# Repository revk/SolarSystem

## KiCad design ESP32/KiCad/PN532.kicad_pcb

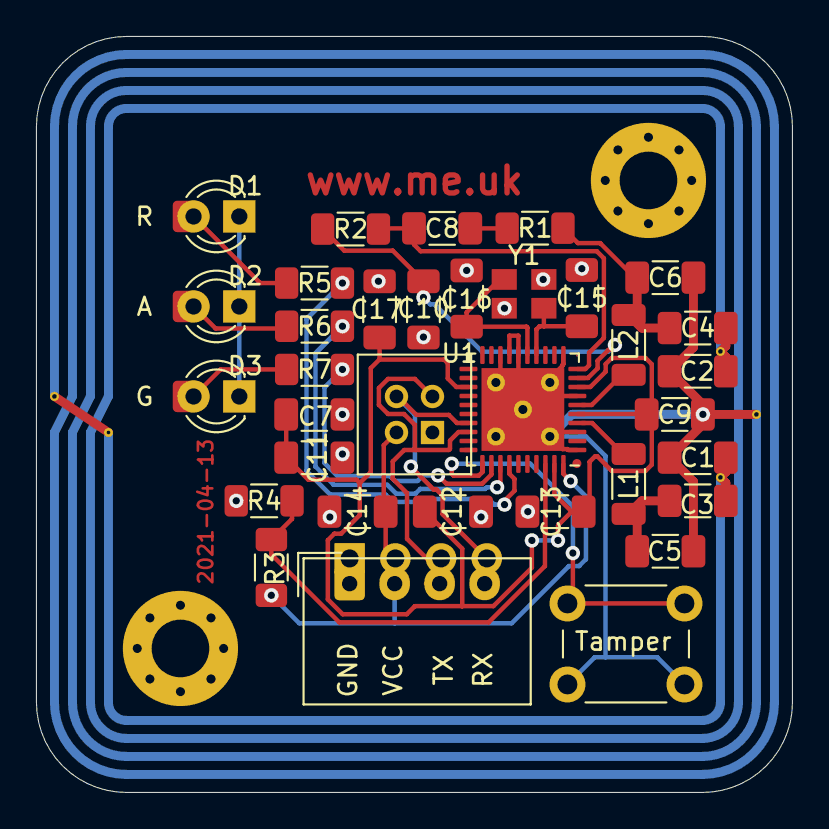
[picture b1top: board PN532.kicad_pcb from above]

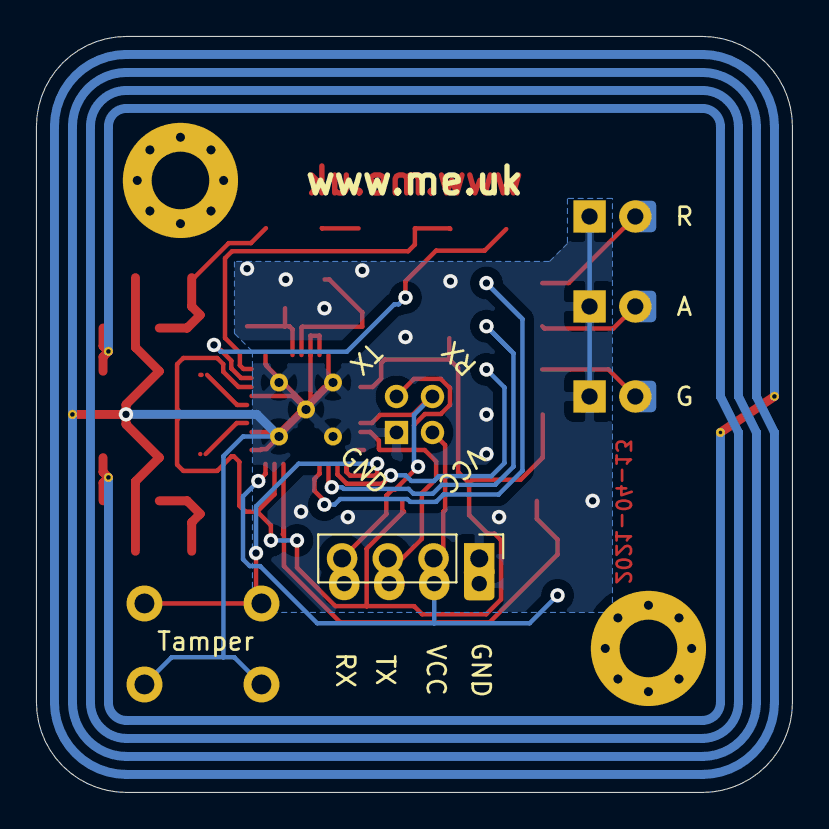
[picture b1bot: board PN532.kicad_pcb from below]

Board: 2 copper layers, 42.0 x 42.0 mm, 38 parts (2 on the bottom side), 24 nets.

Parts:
A1: PN532-Antenna
C1, C2: 200pF; C_1206_3216Metric_Pad1.33x1.80mm_HandSolder
C3, C4, C15, C16: 22pF; C_1206_3216Metric_Pad1.33x1.80mm_HandSolder
C5, C6: 220pF; C_1206_3216Metric_Pad1.33x1.80mm_HandSolder
C7, C10, C11, C12, C14, C17: 0.1uF; C_1206_3216Metric_Pad1.33x1.80mm_HandSolder
C8: 1nF; C_1206_3216Metric_Pad1.33x1.80mm_HandSolder
C9: 4.7uF; C_1206_3216Metric_Pad1.33x1.80mm_HandSolder
C13: 10uF; C_1206_3216Metric_Pad1.33x1.80mm_HandSolder
D1: RED; LED_D3.0mm_and_SMD
D2: AMBER; LED_D3.0mm_and_SMD
D3: GREEN; LED_D3.0mm_and_SMD
H1, H2: MountingHole; MountingHole_3.2mm_M3_Pad_Via
J1: Header; PinHeader_1x04_P2.54mm_Vertical
J2: SPOX; Molex_SPOX_5268-04A_1x04_P2.50mm_Horizontal
J3: MiniGrid; Connector-MilliGrid-2x2
L1, L2: 560nH; L_1206_3216Metric_Pad1.22x1.90mm_HandSolder
R1: 1K6; R_1206_3216Metric_Pad1.30x1.75mm_HandSolder
R2, R5, R6, R7: 1K; R_1206_3216Metric_Pad1.30x1.75mm_HandSolder
R3: 10K; R_1206_3216Metric_Pad1.30x1.75mm_HandSolder
R4: 20K; R_1206_3216Metric_Pad1.30x1.75mm_HandSolder
SW1: TAMPER; SW_PUSH_6mm
U1: PN532; QFN-40-(hand)-1EP_6x6mm_P0.5mm_EP4.6x4.6mm
Y1: 27.12MHz (Mouser 830053099); Crystal-3.4x2.7

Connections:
+3V3: C7.1, C9.1, C11.1, C12.1, C13.1, C17.1, U1.5, U1.8, U1.23, U1.39
+5V: C14.1, J1.2, J2.2, J3.2, R3.2, U1.40
GND: A1.2, C1.2, C2.1, C5.1, C6.1, C7.2, C9.2, C10.2, C11.2, C12.2, C13.2, C14.2, C15.2, C16.2, C17.2, D1.1, D2.1, D3.1, J1.1, J2.1, J3.1, R4.1, SW1.1, U1.1, U1.3, U1.7, U1.11, U1.16, U1.17, U1.18, U1.41, Y1.2, Y1.4
unnamed: A1.1, C1.1, C3.2
unnamed: A1.3, C2.2, C4.1
unnamed: C3.1, C5.2, L1.2
unnamed: C4.2, C6.2, L2.1, R1.2
unnamed: C8.1, R2.1, U1.10
unnamed: C8.2, R1.1
unnamed: C10.1, R2.2, U1.9
unnamed: C15.1, U1.14, Y1.1
unnamed: C16.1, U1.15, Y1.3
unnamed: D1.2, R5.2
unnamed: D2.2, R6.2
unnamed: D3.2, R7.2
unnamed: J1.3, J2.3, J3.3, U1.28
unnamed: J1.4, J2.4, J3.4, U1.27
unnamed: L1.1, U1.4
unnamed: L2.2, U1.6
unnamed: R3.1, R4.2, U1.38
unnamed: R5.1, U1.34
unnamed: R6.1, U1.33
unnamed: R7.1, U1.32
unnamed: SW1.2, U1.31

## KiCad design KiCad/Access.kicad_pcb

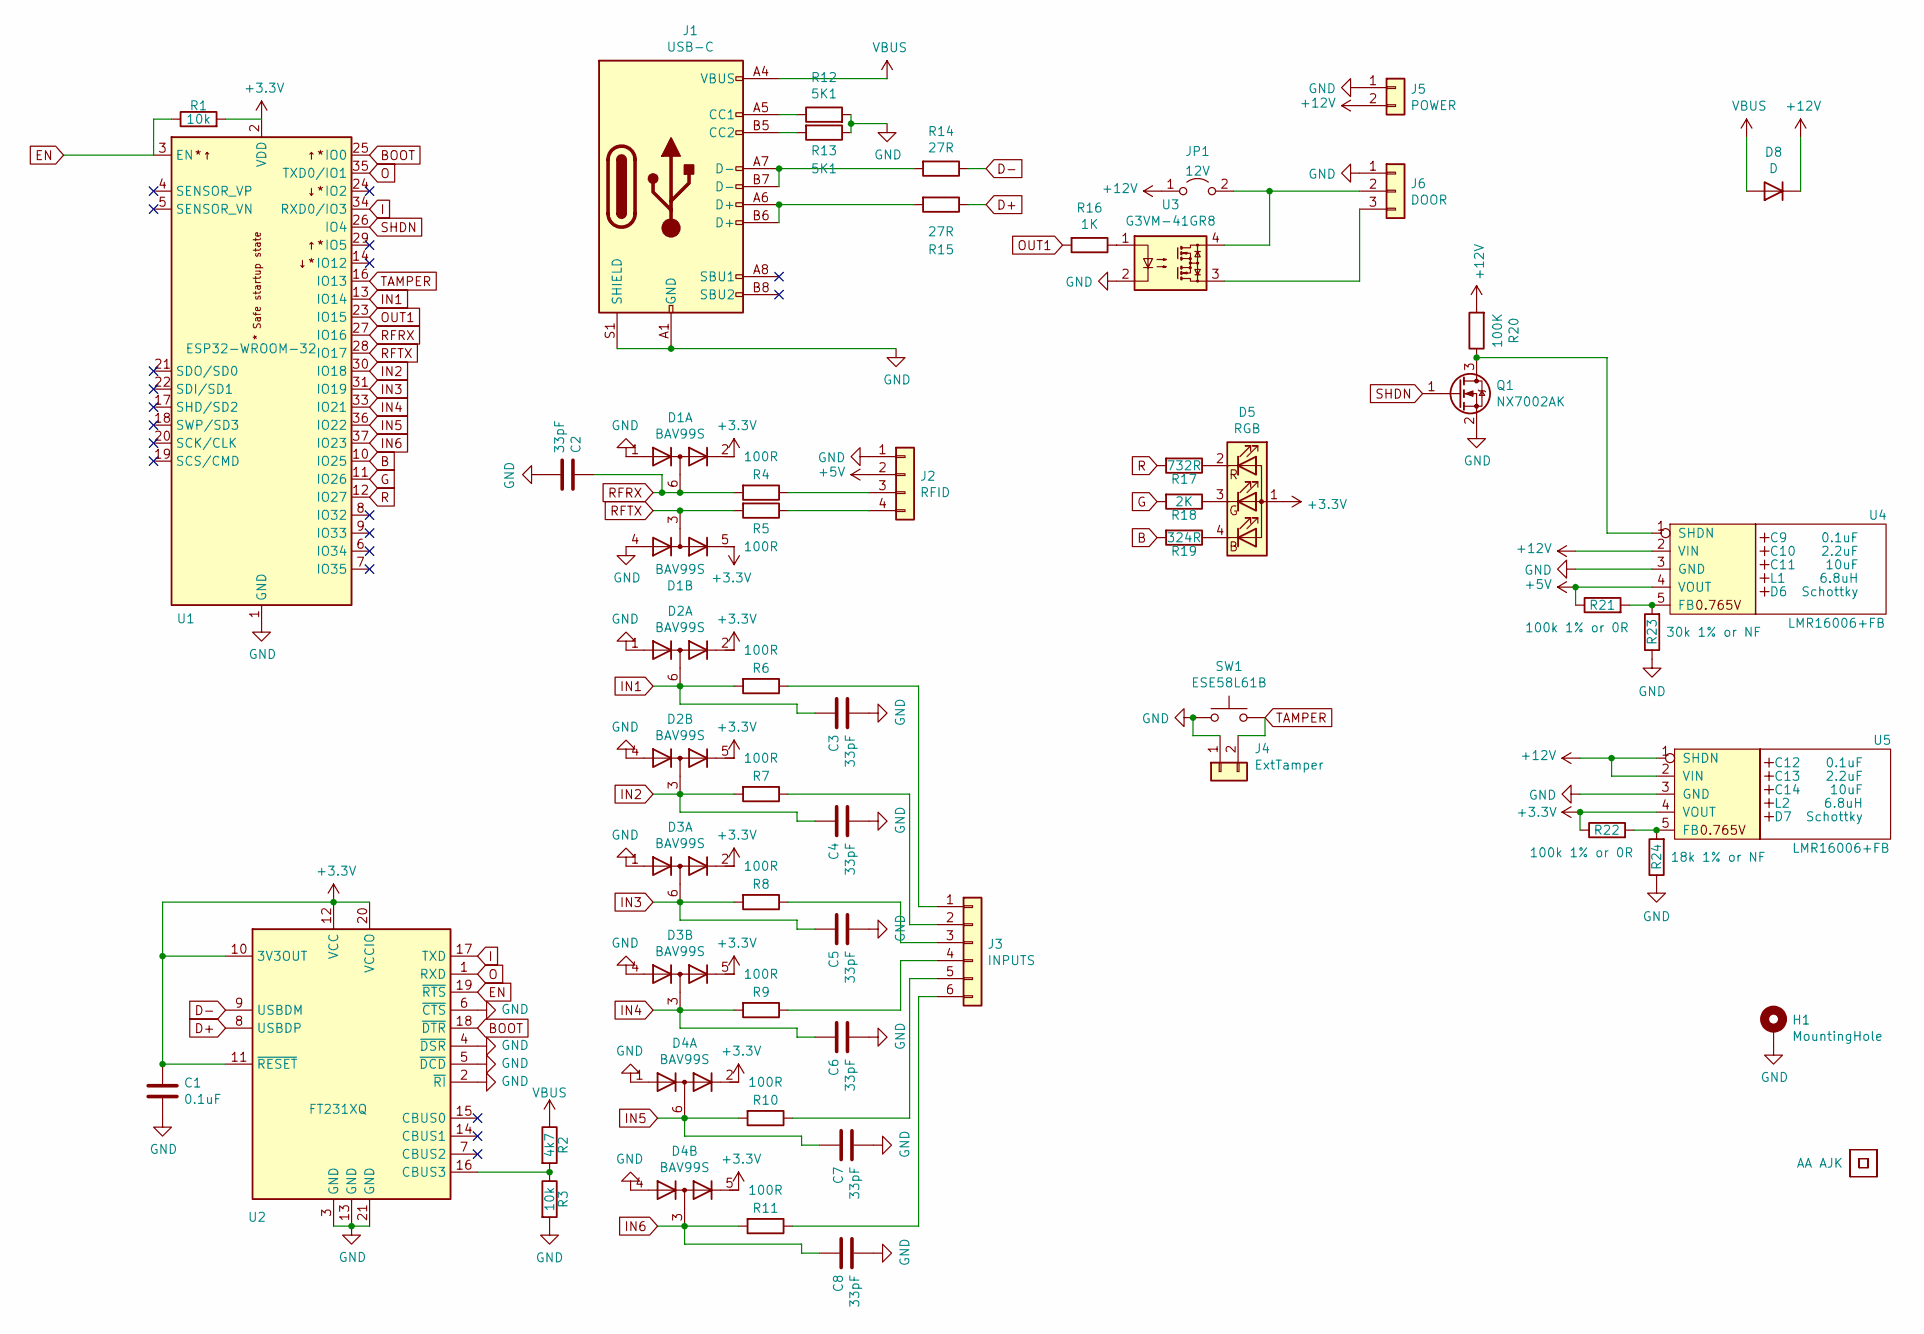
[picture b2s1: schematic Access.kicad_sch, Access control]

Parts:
AJK1: AJK
C1: 0.1uF; C_0603
C2, C3, C4, C5, C6, C7, C8: 33pF; C_0603
C9, C12: 0.1uF; Hidden
C10, C13: 2.2uF; Hidden
C11, C14: 10uF; Hidden
D1, D2, D3, D4: BAV99S; SOT-363_SC-70-6
D5: RGB; LED-RGB-1.6x1.6; Part No APTF1616LSEEZGKQBKC
D6, D7: Schottky; Hidden; Part No CD1206-B2100
D8: D; D_1206_3216Metric_Pad1.42x1.75mm_HandSolder
H1: MountingHole; ISO7380-M3-Pad
J1: USB-C; USC16-TR-Round
J2: RFID; Molex_MiniSPOX_H4RA
J3: INPUTS; Molex_MiniSPOX_H6RA
J4: ExtTamper; PinHeader_1x02_P2.54mm_Vertical
J5: POWER; Molex_MiniSPOX_H2RA
J6: DOOR; Molex_MiniSPOX_H3RA
JP1: 12V; PinHeader_1x02_P1.27mm_Vertical
L1, L2: 6.8uH; Hidden; Part No TYA4020
Q1: NX7002AK; SOT-23; Part No NX7002AK
R1, R3: 10k; R_0603
R2: 4k7; R_0603
R4, R5, R6, R7, R8, R9, R10, R11: 100R; R_0603
R12, R13: 5K1; R_0603
R14, R15: 27R; R_0603
R16: 1K; R_0603_1608Metric_Pad0.98x0.95mm_HandSolder
R17: 732R; R_0603
R18: 2K; R_0603
R19: 324R; R_0603
R20: 100K; R_0603
R21, R22: 100k 1% or 0R; R_0603
R23: 30k 1% or NF; R_0603
R24: 18k 1% or NF; R_0603
SW1: ESE58L61B; ESE58
U1: ESP32-WROOM-32
U2: FT231XQ; QFN-20-1EP_4x4mm_P0.5mm_EP2.5x2.5mm
U3: G3VM-41GR8; Special-SOP-4-3.7x4.55
U4, U5: LMR16006+FB; RegulatorBlockFB; Part No LMR16006YQ3
U6: AA
U7: QR; QR-SS

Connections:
+3V3: C1.1, D1.2 (K2), D1.5 (K4), D2.2 (K2), D2.5 (K4), D3.2 (K2), D3.5 (K4), D4.2 (K2), D4.5 (K4), D5.1 (A), R1.2, R22.1, U1.2 (VDD), U2.10 (3V3OUT), U2.11 (~RESET), U2.12 (VCC), U2.20 (VCCIO), U5.4 (VOUT)
+5V: J2.2, R21.1, U4.4 (VOUT)
+12V: D8.1 (K), J5.2, JP1.1 (A), R20.2, U4.2 (VIN), U5.1 (SHDN), U5.2 (VIN)
B: R19.2, U1.10 (IO25)
BOOT: U1.25 (IO0), U2.18 (~DTR)
D+: R15.1, U2.8 (USBDP)
D-: R14.1, U2.9 (USBDM)
EN: R1.1, U1.3 (EN), U2.19 (~RTS)
G: R18.2, U1.11 (IO26)
GND: C1.2, C2.2, C3.2, C4.2, C5.2, C6.2, C7.2, C8.2, D1.1 (A1), D1.4 (A3), D2.1 (A1), D2.4 (A3), D3.1 (A1), D3.4 (A3), D4.1 (A1), D4.4 (A3), H1.1, J1.A1 (GND), J1.A12 (GND), J1.B1 (GND), J1.B12 (GND), J1.S1 (SHIELD), J2.1, J4.1, J5.1, J6.1, Q1.2 (S), R3.2, R12.2, R13.1, R23.1, R24.1, SW1.1, U1.1 (GND), U1.15 (GND), U1.38 (GND), U1.39 (GND), U2.2 (~RI), U2.3 (GND), U2.4 (~DSR), U2.5 (~DCD), U2.6 (~CTS), U2.13 (GND), U2.21 (GND), U3.2, U4.3 (GND), U5.3 (GND)
I: U1.34 (RXD0/IO3), U2.17 (TXD)
IN1: C3.1, D2.6 (K3A4), R6.2, U1.13 (IO14)
IN2: C4.1, D2.3 (K1A2), R7.2, U1.30 (IO18)
IN3: C5.1, D3.6 (K3A4), R8.2, U1.31 (IO19)
IN4: C6.1, D3.3 (K1A2), R9.2, U1.33 (IO21)
IN5: C7.1, D4.6 (K3A4), R10.2, U1.36 (IO22)
IN6: C8.1, D4.3 (K1A2), R11.2, U1.37 (IO23)
unnamed: D5.2 (RK), R17.1
unnamed: D5.3 (GK), R18.1
unnamed: D5.4 (BK), R19.1
unnamed: J1.A5 (CC1), R12.1
unnamed: J1.A6 (D+), J1.B6 (D+), R15.2
unnamed: J1.A7 (D-), J1.B7 (D-), R14.2
unnamed: J1.B5 (CC2), R13.2
unnamed: J2.3, R4.1
unnamed: J2.4, R5.1
unnamed: J3.1, R6.1
unnamed: J3.2, R7.1
unnamed: J3.3, R8.1
unnamed: J3.4, R9.1
unnamed: J3.5, R10.1
unnamed: J3.6, R11.1
unnamed: J6.2, JP1.2 (B), U3.4
unnamed: J6.3, U3.3
unnamed: Q1.3 (D), R20.1, U4.1 (SHDN)
unnamed: R2.2, R3.1, U2.16 (CBUS3)
unnamed: R16.1, U3.1
unnamed: R21.2, R23.2, U4.5 (FB)
unnamed: R22.2, R24.2, U5.5 (FB)
O: U1.35 (TXD0/IO1), U2.1 (RXD)
OUT1: R16.2, U1.23 (IO15)
R: R17.2, U1.12 (IO27)
RFRX: C2.1, D1.6 (K3A4), R4.2, U1.27 (IO16)
RFTX: D1.3 (K1A2), R5.2, U1.28 (IO17)
SHDN: Q1.1 (G), U1.26 (IO4)
TAMPER: J4.2, SW1.2, U1.16 (IO13)
VBUS: D8.2 (A), J1.A4 (VBUS), J1.A9 (VBUS), J1.B4 (VBUS), J1.B9 (VBUS), R2.1

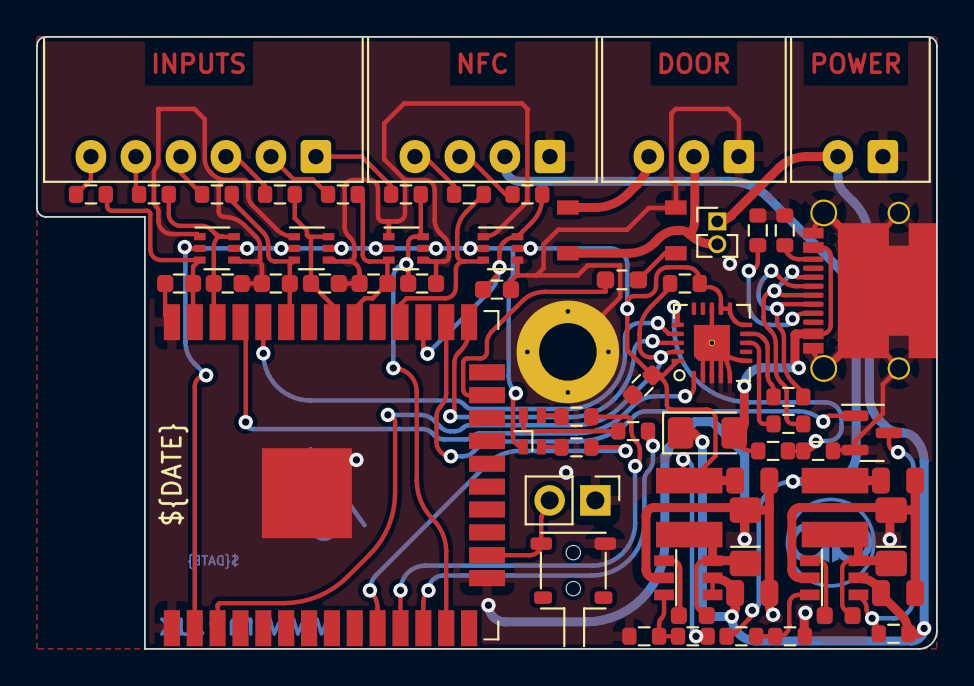
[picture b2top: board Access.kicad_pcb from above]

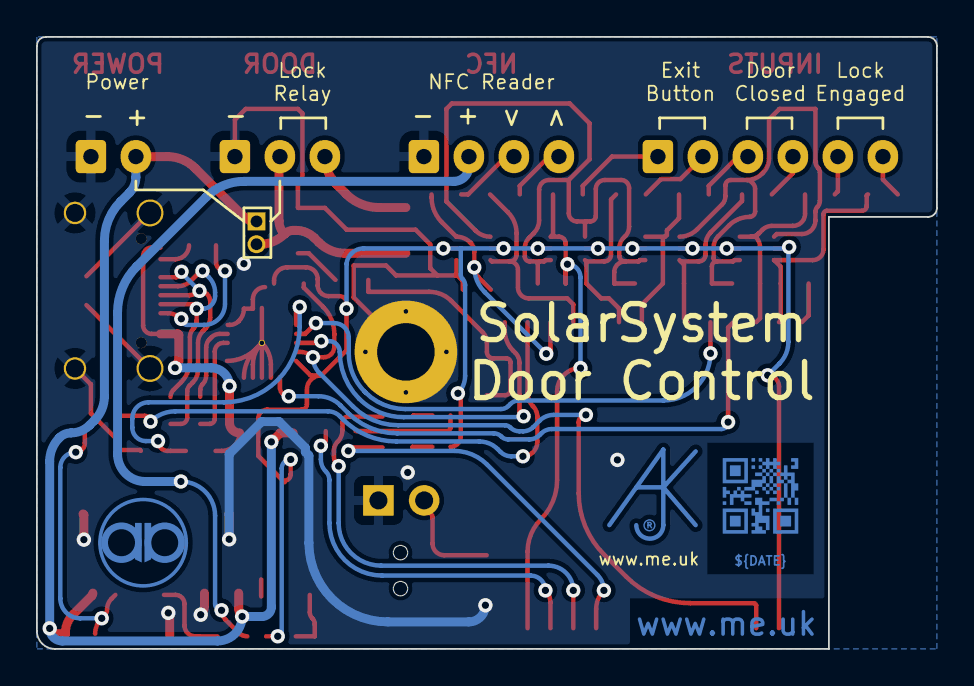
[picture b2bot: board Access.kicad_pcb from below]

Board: 2 copper layers, 50.0 x 34.0 mm, 66 parts (3 on the bottom side), 47 nets.

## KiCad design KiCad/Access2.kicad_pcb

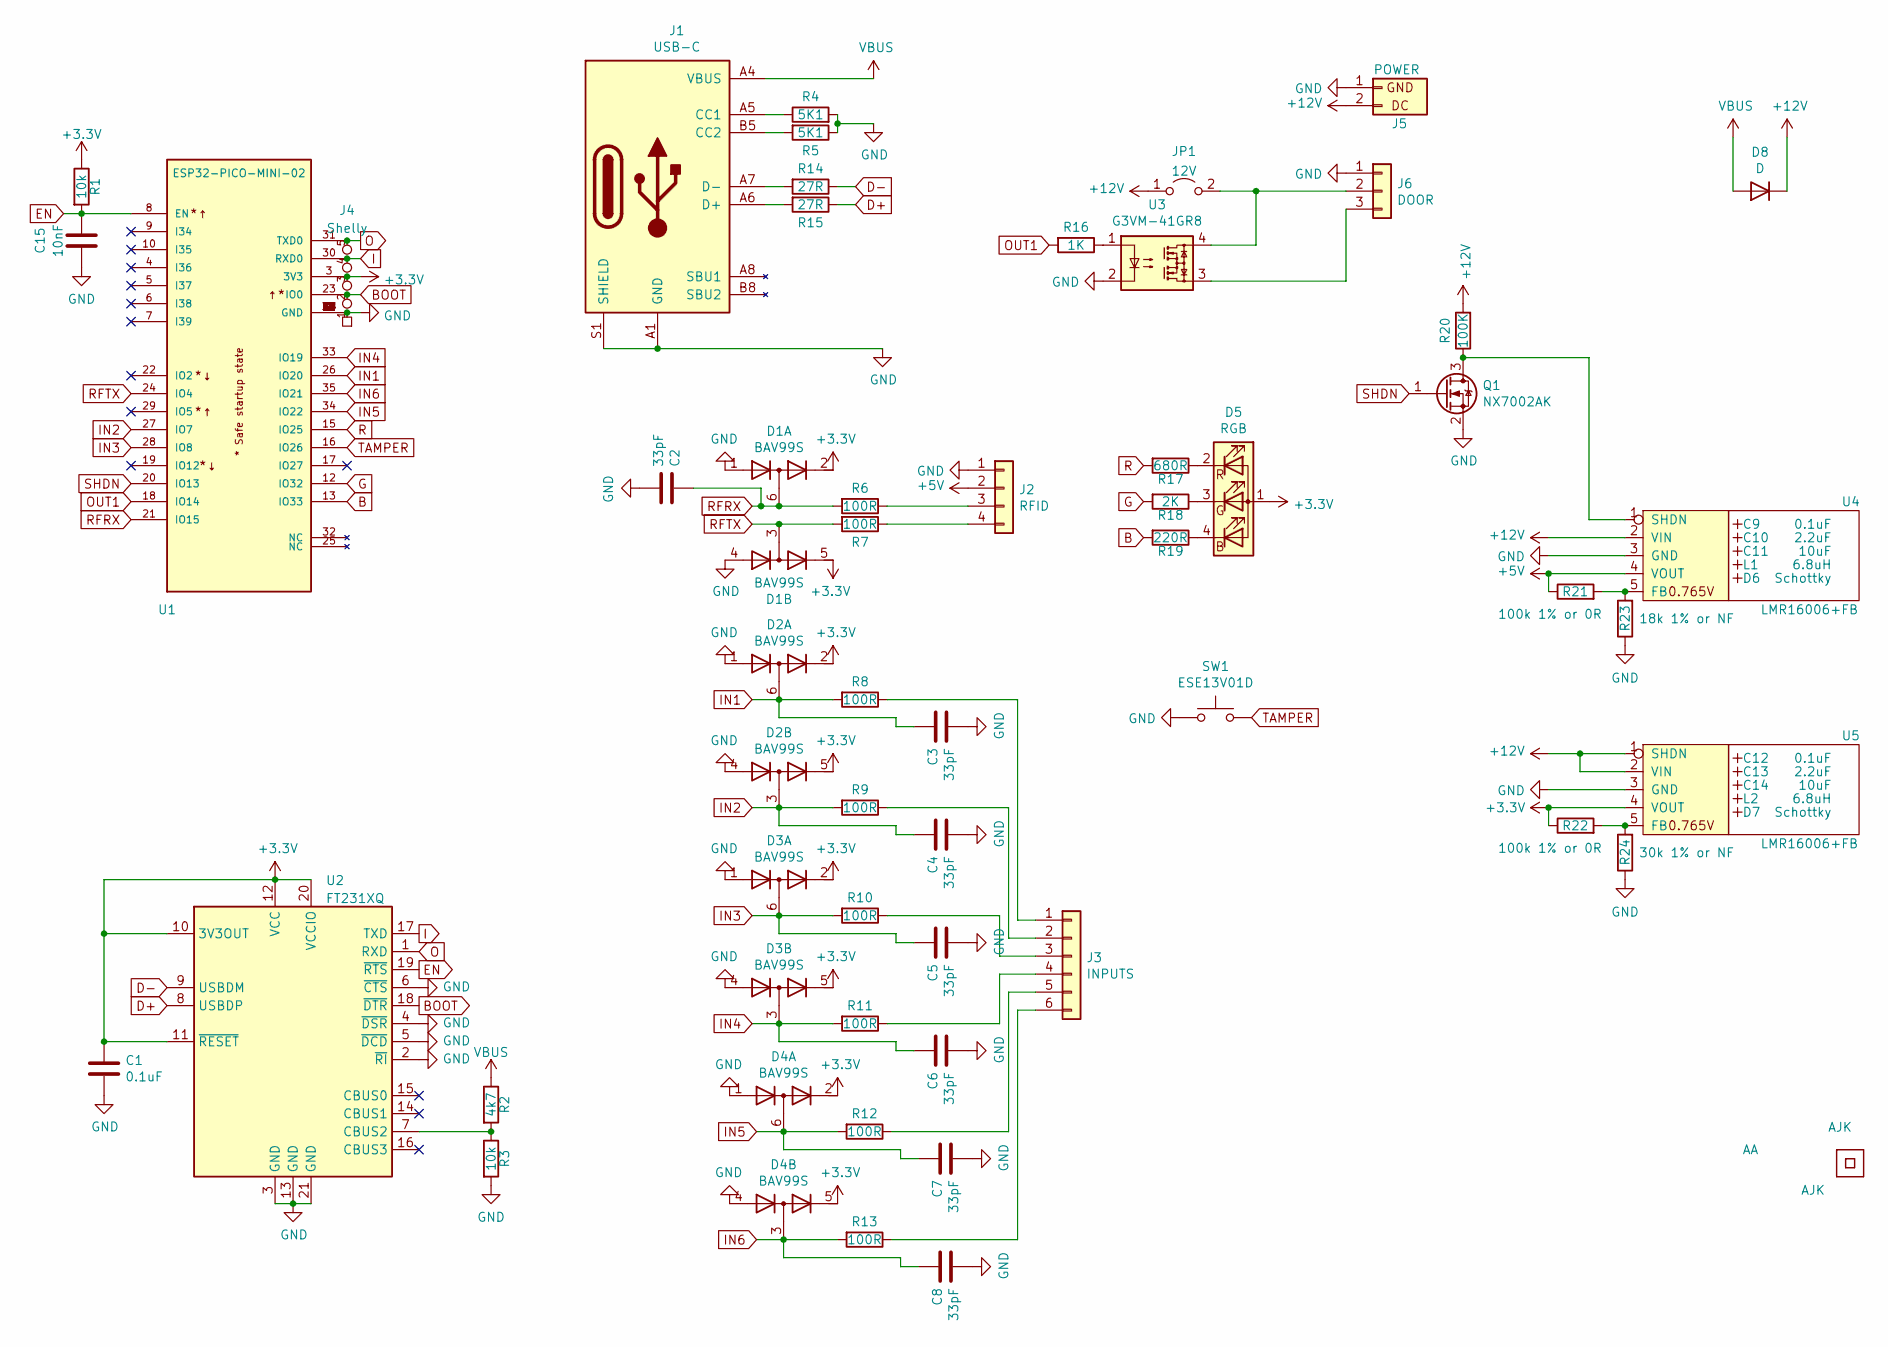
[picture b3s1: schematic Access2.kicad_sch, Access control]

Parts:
AJK1: AJK
C1: 0.1uF; C_0603
C2, C3, C4, C5, C6, C7, C8: 33pF; C_0603
C9, C12: 0.1uF; C_0603_
C10, C13: 2.2uF; C_0805_
C11, C14: 10uF; C_0805_
C15: 10nF; C_0603
D1, D2, D3, D4: BAV99S; SOT-363_SC-70-6
D5: RGB; LED-RGB-1.6x1.6; Part No APTF1616LSEEZGKQBKC
D6, D7: Schottky; D_1206_; Part No CD1206-B2100
D8: D; D_1206
J1: USB-C; USC16-TR
J2: RFID; Molex_MiniSPOX_H4RA
J3: INPUTS; Molex_MiniSPOX_H6RA
J4: Shelly
J5: POWER; Molex_MiniSPOX_H2RA
J6: DOOR; Molex_MiniSPOX_H3RA
JP1: 12V; PinHeader_1x02_P1.27mm_Vertical
L1, L2: 6.8uH; L_4x4_; Part No TYA4020
Logo1: AJK
Q1: NX7002AK; SOT-23; Part No NX7002AK
R1, R3: 10k; R_0603
R2: 4k7; R_0603
R4, R5: 5K1; R_0603
R6, R7, R8, R9, R10, R11, R12, R13: 100R; R_0603
R14, R15: 27R; R_0603
R16: 1K; R_0603
R17: 680R; R_0603
R18: 2K; R_0603
R19: 220R; R_0603
R20: 100K; R_0603
R21, R22: 100k 1% or 0R; R_0603
R23: 18k 1% or NF; R_0603
R24: 30k 1% or NF; R_0603
SW1: ESE13V01D; ESE13
U1: ESP32-PICO-MINI-02; PARTREV v1.0
U2: FT231XQ; QFN-20-1EP_4x4mm_P0.5mm_EP2.5x2.5mm
U3: G3VM-41GR8; Special-SOP-4-3.7x4.55
U4, U5: LMR16006+FB; SOT-23-Thin-6-Reg; Part No LMR16006YQ3
U6: AA
U7: QR; QR-SS

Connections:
+3V3: C1.1, D1.2 (K2), D1.5 (K4), D2.2 (K2), D2.5 (K4), D3.2 (K2), D3.5 (K4), D4.2 (K2), D4.5 (K4), D5.1 (A), J4.3 (3V3), R1.1, R22.1, U1.3 (3V3), U2.10 (3V3OUT), U2.11 (~RESET), U2.12 (VCC), U2.20 (VCCIO), U5.4 (VOUT)
+5V: J2.2, R21.1, U4.4 (VOUT)
+12V: D8.1 (K), J5.2 (DC), JP1.1 (A), R20.2, U4.2 (VIN), U5.1 (SHDN), U5.2 (VIN)
B: R19.2, U1.13 (IO33)
BOOT: J4.2 (0), U1.23 (IO0), U2.18 (~DTR)
D+: R15.1, U2.8 (USBDP)
D-: R14.1, U2.9 (USBDM)
EN: C15.2, R1.2, U1.8 (EN), U2.19 (~RTS)
G: R18.2, U1.12 (IO32)
GND: C1.2, C2.2, C3.2, C4.2, C5.2, C6.2, C7.2, C8.2, C15.1, D1.1 (A1), D1.4 (A3), D2.1 (A1), D2.4 (A3), D3.1 (A1), D3.4 (A3), D4.1 (A1), D4.4 (A3), J1.A1 (GND), J1.A12 (GND), J1.B1 (GND), J1.B12 (GND), J1.S1 (SHIELD), J2.1, J4.1 (GND), J5.1 (GND), J6.1, Q1.2 (S), R3.2, R4.2, R5.1, R23.1, R24.1, SW1.1, U1.1 (GND), U1.2 (GND), U1.11 (GND), U1.14 (GND), U1.36 (GND), U1.37 (GND), U1.38 (GND), U1.39 (GND), U1.40 (GND), U1.41 (GND), U1.42 (GND), U1.43 (GND), U1.44 (GND), U1.45 (GND), U1.46 (GND), U1.47 (GND), U1.48 (GND), U1.49 (GND), U1.50 (GND), U1.51 (GND), U1.52 (GND), U1.53 (GND), U2.2 (~RI), U2.3 (GND), U2.4 (~DSR), U2.5 (~DCD), U2.6 (~CTS), U2.13 (GND), U2.21 (GND), U3.2, U4.3 (GND), U5.3 (GND)
I: J4.4 (Rx), U1.30 (RXD0), U2.17 (TXD)
IN1: C3.1, D2.6 (K3A4), R8.2, U1.26 (IO20)
IN2: C4.1, D2.3 (K1A2), R9.2, U1.27 (IO7)
IN3: C5.1, D3.6 (K3A4), R10.2, U1.28 (IO8)
IN4: C6.1, D3.3 (K1A2), R11.2, U1.33 (IO19)
IN5: C7.1, D4.6 (K3A4), R12.2, U1.34 (IO22)
IN6: C8.1, D4.3 (K1A2), R13.2, U1.35 (IO21)
unnamed: D5.2 (RK), R17.1
unnamed: D5.3 (GK), R18.1
unnamed: D5.4 (BK), R19.1
unnamed: J1.A5 (CC1), R4.1
unnamed: J1.A6 (D+), J1.B6 (D+), R15.2
unnamed: J1.A7 (D-), J1.B7 (D-), R14.2
unnamed: J1.B5 (CC2), R5.2
unnamed: J2.3, R6.1
unnamed: J2.4, R7.1
unnamed: J3.1, R8.1
unnamed: J3.2, R9.1
unnamed: J3.3, R10.1
unnamed: J3.4, R11.1
unnamed: J3.5, R12.1
unnamed: J3.6, R13.1
unnamed: J6.2, JP1.2 (B), U3.4
unnamed: J6.3, U3.3
unnamed: Q1.3 (D), R20.1, U4.1 (SHDN)
unnamed: R2.2, R3.1, U2.7 (CBUS2)
unnamed: R16.1, U3.1
unnamed: R21.2, R23.2, U4.5 (FB)
unnamed: R22.2, R24.2, U5.5 (FB)
O: J4.5 (Tx), U1.31 (TXD0), U2.1 (RXD)
OUT1: R16.2, U1.18 (IO14)
R: R17.2, U1.15 (IO25)
RFRX: C2.1, D1.6 (K3A4), R6.2, U1.21 (IO15)
RFTX: D1.3 (K1A2), R7.2, U1.24 (IO4)
SHDN: Q1.1 (G), U1.20 (IO13)
TAMPER: SW1.2, U1.16 (IO26)
VBUS: D8.2 (A), J1.A4 (VBUS), J1.A9 (VBUS), J1.B4 (VBUS), J1.B9 (VBUS), R2.1

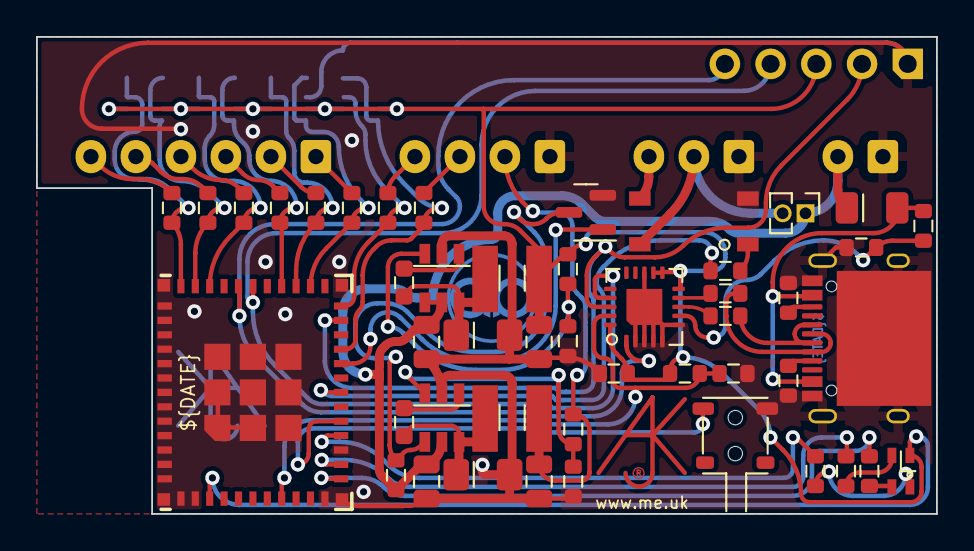
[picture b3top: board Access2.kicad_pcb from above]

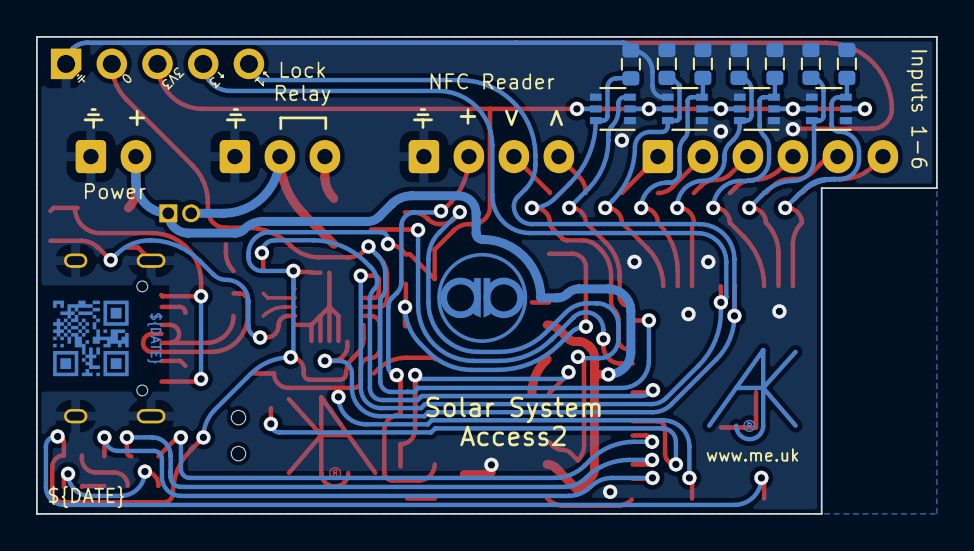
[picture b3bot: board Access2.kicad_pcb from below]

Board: 2 copper layers, 50.0 x 26.5 mm, 67 parts (15 on the bottom side), 47 nets.

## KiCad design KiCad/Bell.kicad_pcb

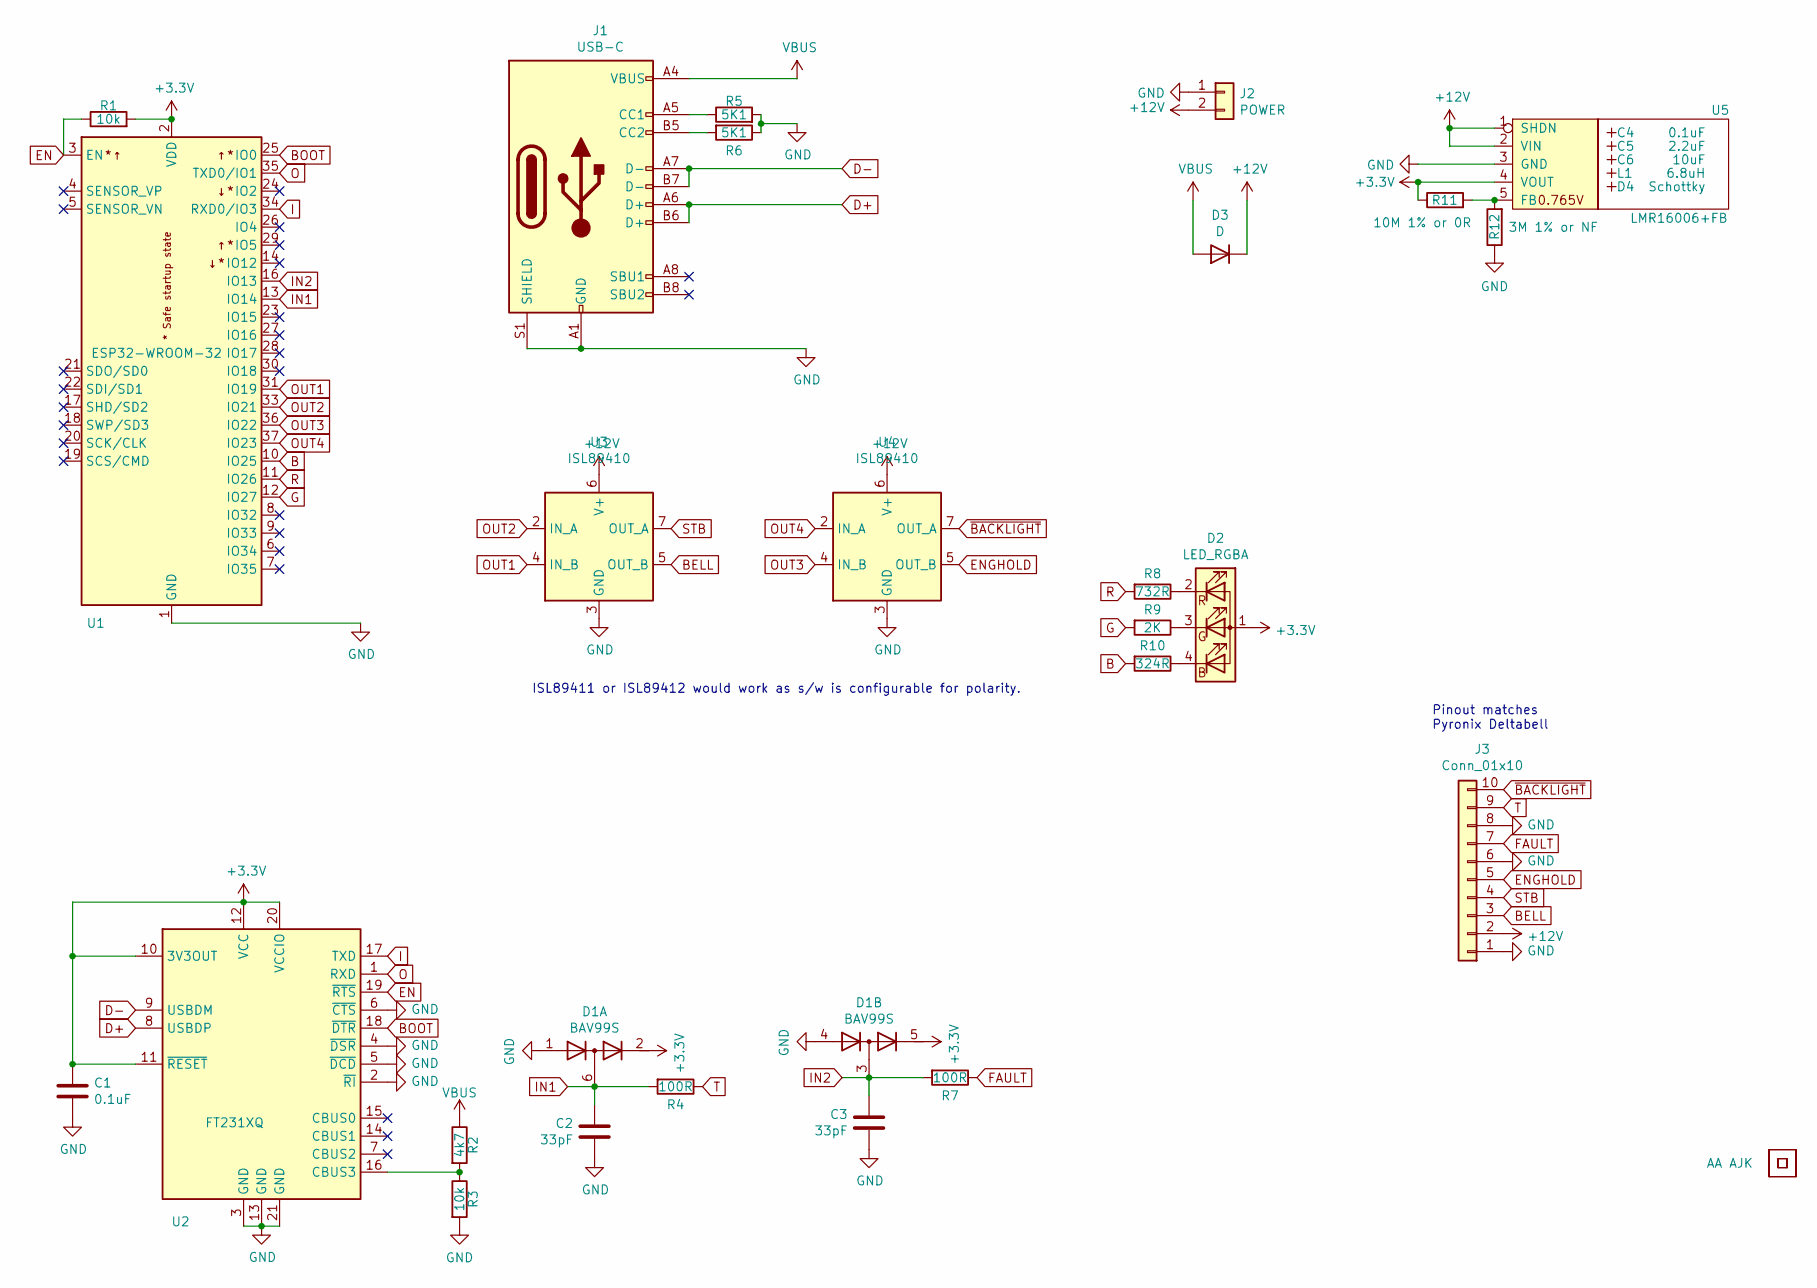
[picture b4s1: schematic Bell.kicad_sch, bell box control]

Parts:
AJK1: AJK
C1: 0.1uF; C_0603
C2, C3: 33pF; C_0603
C4: 0.1uF; Hidden
C5: 2.2uF; Hidden
C6: 10uF; Hidden
D1: BAV99S; SOT-363_SC-70-6
D2: LED_RGBA; LED-RGB-1.6x1.6
D3: D; D_1206_3216Metric_Pad1.42x1.75mm_HandSolder
D4: Schottky; Hidden; Part No CD1206-B2100
J1: USB-C; USC16-TR-Round
J2: POWER; Molex_MiniSPOX_H2RA
J3: Conn_01x10; Molex_MiniSPOX_H10RA
L1: 6.8uH; Hidden; Part No TYA4020
R1, R3: 10k; R_0603
R2: 4k7; R_0603
R4, R7: 100R; R_0603
R5, R6: 5K1; R_0603
R8: 732R; R_0603
R9: 2K; R_0603
R10: 324R; R_0603
R11: 10M 1% or 0R; R_0603
R12: 3M 1% or NF; R_0603
U1: ESP32-WROOM-32
U2: FT231XQ; QFN-20-1EP_4x4mm_P0.5mm_EP2.5x2.5mm
U3, U4: ISL89410; SO-8_3.9x4.9mm_P1.27mm
U5: LMR16006+FB; RegulatorBlockFB; Part No LMR16006YQ3
U6: AA
U7: QR; QR-SS

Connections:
+3V3: C1.1, D1.2 (K2), D1.5 (K4), D2.1 (A), R1.2, R11.1, U1.2 (VDD), U2.10 (3V3OUT), U2.11 (~RESET), U2.12 (VCC), U2.20 (VCCIO), U5.4 (VOUT)
+12V: D3.1 (K), J2.2, J3.2, U3.6 (V+), U4.6 (V+), U5.1 (SHDN), U5.2 (VIN)
B: R10.2, U1.10 (IO25)
BELL: J3.3, U3.5 (OUT_B)
BOOT: U1.25 (IO0), U2.18 (~DTR)
D+: J1.A6 (D+), J1.B6 (D+), U2.8 (USBDP)
D-: J1.A7 (D-), J1.B7 (D-), U2.9 (USBDM)
EN: R1.1, U1.3 (EN), U2.19 (~RTS)
ENGHOLD: J3.5, U4.5 (OUT_B)
FAULT: J3.7, R7.1
G: R9.2, U1.12 (IO27)
GND: C1.2, C2.2, C3.2, D1.1 (A1), D1.4 (A3), J1.A1 (GND), J1.A12 (GND), J1.B1 (GND), J1.B12 (GND), J1.S1 (SHIELD), J2.1, J3.1, J3.6, J3.8, R3.2, R5.2, R6.1, R12.1, U1.1 (GND), U1.15 (GND), U1.38 (GND), U1.39 (GND), U2.2 (~RI), U2.3 (GND), U2.4 (~DSR), U2.5 (~DCD), U2.6 (~CTS), U2.13 (GND), U2.21 (GND), U3.3 (GND), U4.3 (GND), U5.3 (GND)
I: U1.34 (RXD0/IO3), U2.17 (TXD)
IN1: C2.1, D1.6 (K3A4), R4.2, U1.13 (IO14)
IN2: C3.1, D1.3 (K1A2), R7.2, U1.16 (IO13)
unnamed: D2.2 (RK), R8.1
unnamed: D2.3 (GK), R9.1
unnamed: D2.4 (BK), R10.1
unnamed: J1.A5 (CC1), R5.1
unnamed: J1.B5 (CC2), R6.2
unnamed: R2.2, R3.1, U2.16 (CBUS3)
unnamed: R11.2, R12.2, U5.5 (FB)
O: U1.35 (TXD0/IO1), U2.1 (RXD)
OUT1: U1.31 (IO19), U3.4 (IN_B)
OUT2: U1.33 (IO21), U3.2 (IN_A)
OUT3: U1.36 (IO22), U4.4 (IN_B)
OUT4: U1.37 (IO23), U4.2 (IN_A)
R: R8.2, U1.11 (IO26)
STB: J3.4, U3.7 (OUT_A)
T: J3.9, R4.1
VBUS: D3.2 (A), J1.A4 (VBUS), J1.A9 (VBUS), J1.B4 (VBUS), J1.B9 (VBUS), R2.1
~BACKLIGHT: J3.10, U4.7 (OUT_A)

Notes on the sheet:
Pinout matches Pyronix Deltabell
ISL89411 or ISL89412 would work as s/w is configurable for polarity.

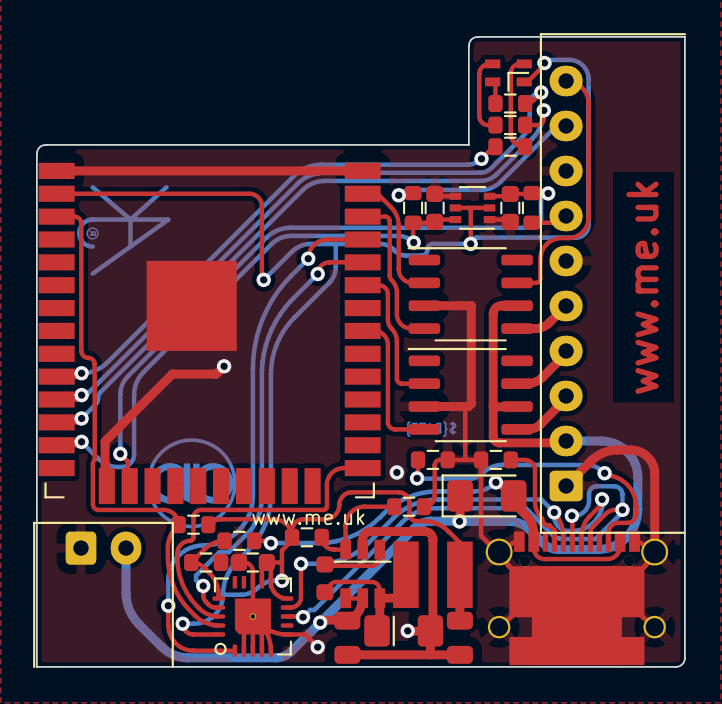
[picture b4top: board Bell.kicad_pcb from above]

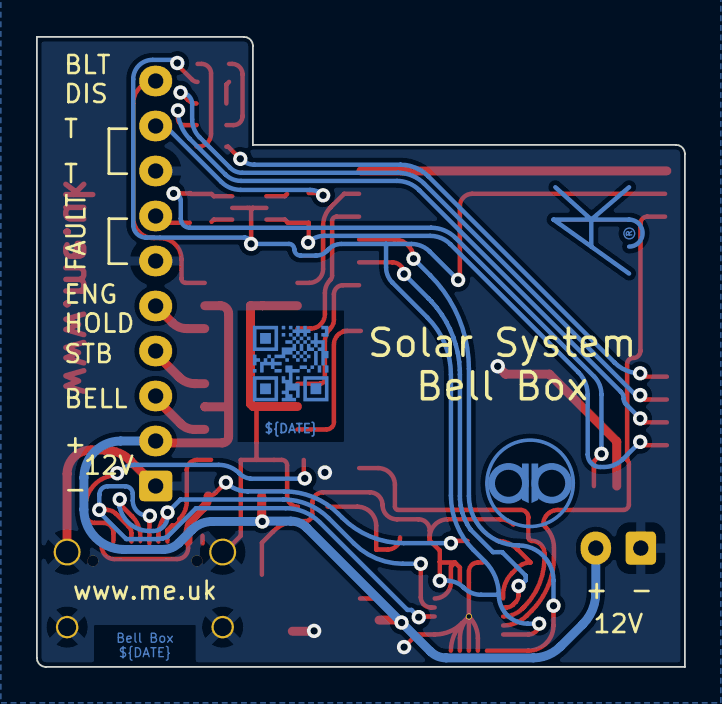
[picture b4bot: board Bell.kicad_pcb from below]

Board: 2 copper layers, 36.0 x 35.0 mm, 34 parts (3 on the bottom side), 32 nets.

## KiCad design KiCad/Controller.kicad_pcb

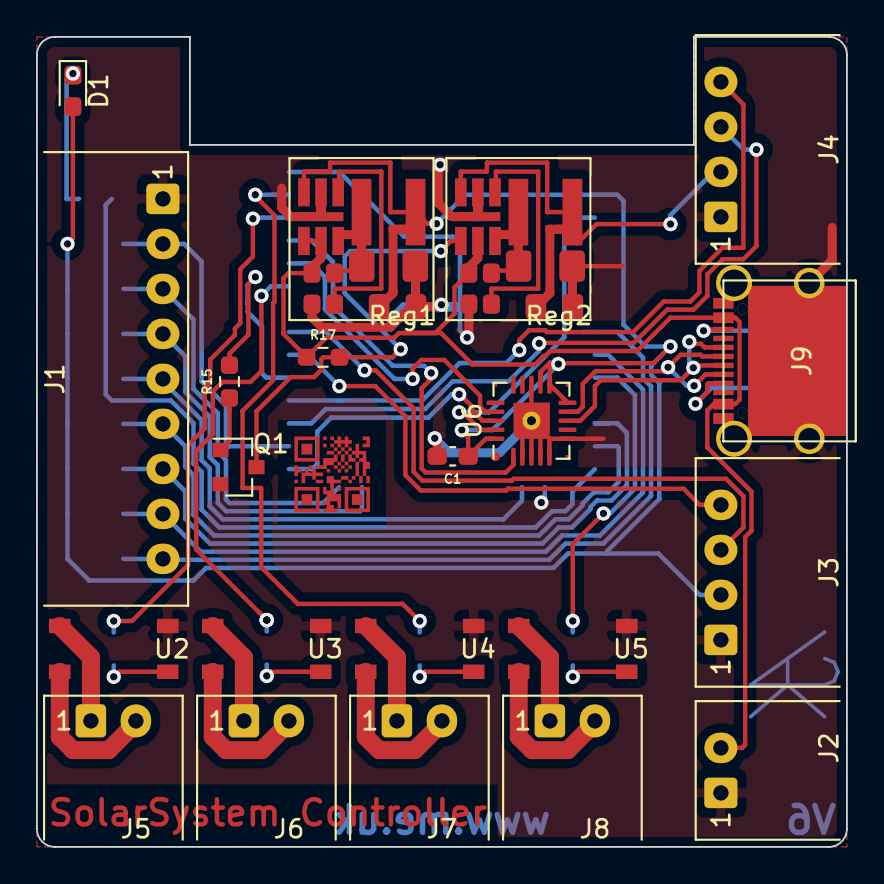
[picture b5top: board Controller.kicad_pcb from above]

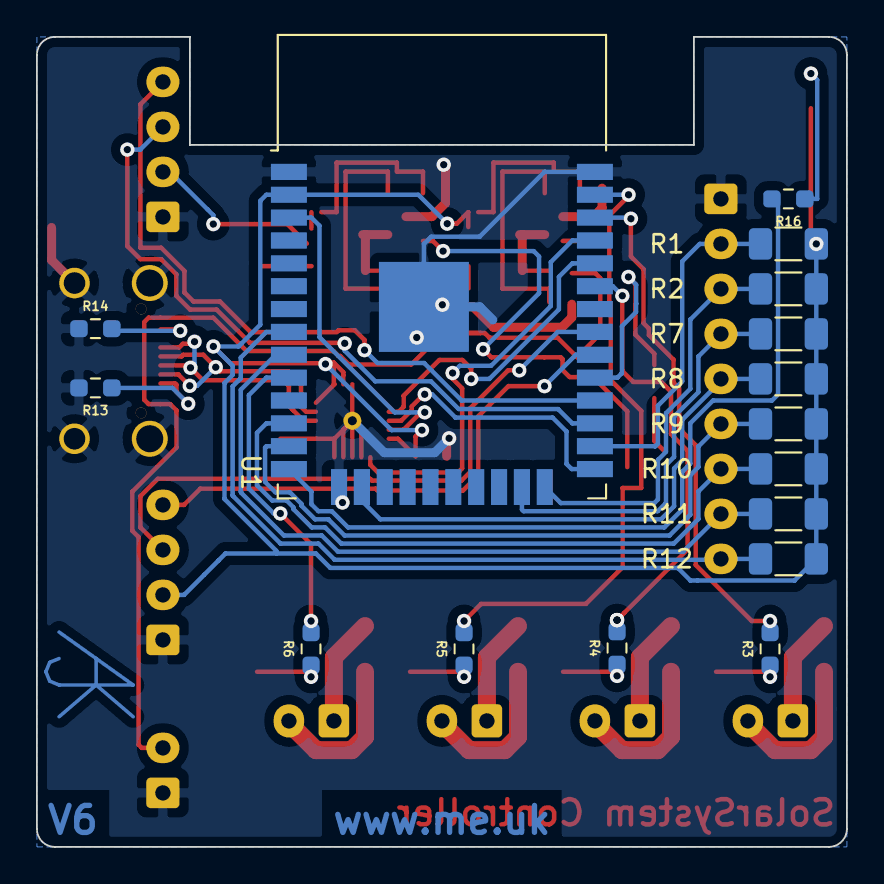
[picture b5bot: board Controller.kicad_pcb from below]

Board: 2 copper layers, 45.0 x 45.0 mm, 39 parts (17 on the bottom side), 45 nets.

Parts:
AJK1: AJK
C1: 0.1uF; C_0603_1608Metric_Pad1.08x0.95mm_HandSolder
D1: LED; LED_0603_1608Metric_Pad1.05x0.95mm_HandSolder
J1: Inputs; Molex_MiniSPOX_H9RA
J2: POWER; Molex_MiniSPOX_H2RA
J3: RANGER; Molex_MiniSPOX_H4RA
J4: RFID; Molex_MiniSPOX_H4RA
J5: OUT1; Molex_MiniSPOX_H2RA
J6: OUT2; Molex_MiniSPOX_H2RA
J7: OUT3; Molex_MiniSPOX_H2RA
J8: OUT4; Molex_MiniSPOX_H2RA
J9: USB-C; USC16-TR-Round
Q1: BC817; SOT-23
R1, R2, R7, R8, R9, R10, R11, R12: NF; R_1206_3216Metric_Pad1.30x1.75mm_HandSolder
R3, R4, R5, R6: 1K; R_0603_1608Metric_Pad0.98x0.95mm_HandSolder
R13, R14: 5K1; R_0603_1608Metric_Pad0.98x0.95mm_HandSolder
R15: 1k; R_0603_1608Metric_Pad0.98x0.95mm_HandSolder
R16: 680R; R_0603_1608Metric_Pad0.98x0.95mm_HandSolder
R17: 100K; R_0603_1608Metric_Pad0.98x0.95mm_HandSolder
Reg1, Reg2: Regulator; RegulatorBlock
U1: ESP32-WROOM-32
U2, U3, U4, U5: G3VM-41GR8; Special-SOP-4-3.7x4.55
U6: FT231XQ; QFN-20-(hand)-1EP_4x4mm_P0.5mm_EP2.5x2.5mm
U7: QR; QR-SS

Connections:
+3V3: C1.1, D1.2, J3.2, R1.1, R2.1, R7.1, R8.1, R9.1, R10.1, R11.1, R12.1, Reg1.4, U1.2, U6.10, U6.11, U6.12, U6.20
+5V: J4.2, Reg2.4
CBUS0: U1.25, U6.18
D+: J9.A6, J9.B6, U6.8
D-: J9.A7, J9.B7, U6.9
EN: U1.3, U6.19
GND: C1.2, J1.1, J2.1, J3.1, J4.1, J9.A1, J9.A12, J9.B1, J9.B12, J9.S1, Q1.2, R13.2, R14.1, Reg1.3, Reg2.3, U1.1, U1.15, U1.38, U1.39, U2.2, U3.2, U4.2, U5.2, U6.2, U6.3, U6.4, U6.5, U6.6, U6.13, U6.21
I: U1.34, U6.17
IN1: J1.2, R1.2, U1.26
IN2: J1.3, R2.2, U1.24
IN3: J1.4, R7.2, U1.23
IN4: J1.5, R8.2, U1.16
IN5: J1.6, R9.2, U1.13
IN6: J1.7, R10.2, U1.12
IN7: J1.8, R11.2, U1.9
IN8: J1.9, R12.2, U1.8
LED: R16.2, U1.14
unnamed: D1.1, R16.1
unnamed: J5.1, U2.3
unnamed: J5.2, U2.4
unnamed: J6.1, U3.3
unnamed: J6.2, U3.4
unnamed: J7.1, U4.3
unnamed: J7.2, U4.4
unnamed: J8.1, U5.3
unnamed: J8.2, U5.4
unnamed: J9.A5, R13.1
unnamed: J9.B5, R14.2
unnamed: Q1.1, R15.1
unnamed: Q1.3, R17.2, Reg2.1
unnamed: R3.1, U2.1
unnamed: R4.1, U3.1
unnamed: R5.1, U4.1
unnamed: R6.1, U5.1
O: U1.35, U6.1
OUT1: R3.2, U1.36
OUT2: R4.2, U1.33
OUT3: R5.2, U1.37
OUT4: R6.2, U1.10
RFRX: J4.3, U1.27
RFTX: J4.4, U1.28
SCL: J3.3, U1.31
SDA: J3.4, U1.30
SHDN: R15.2, U1.29
VBUS: J2.2, J9.A4, J9.A9, J9.B4, J9.B9, R17.1, Reg1.1, Reg1.2, Reg2.2
